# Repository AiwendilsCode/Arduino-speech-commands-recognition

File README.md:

# Arduino speech commands recognition
Arduino speech commands recognition is project in which I tried teach Arduino Nano recognizing words or commands using neural network. This project is inspirated by another [speech commands recognition project by Peter Balch](https://www.instructables.com/Speech-Recognition-With-an-Arduino-Nano/).
Difference between mine and Balch's project is that I used different algorithm for recognizing words.

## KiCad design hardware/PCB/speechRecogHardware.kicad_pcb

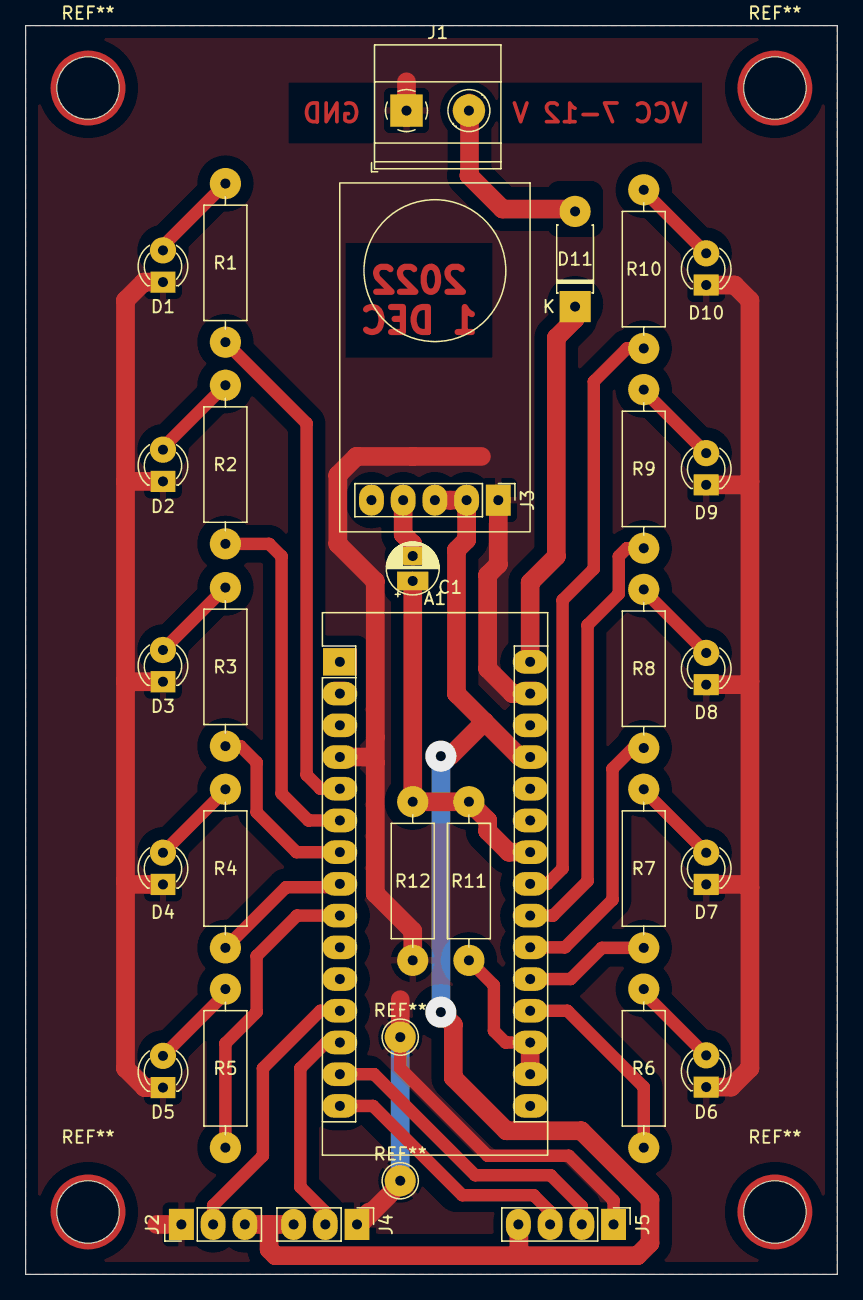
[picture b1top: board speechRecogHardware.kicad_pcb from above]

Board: 2 copper layers, 65.0 x 100.0 mm, 30 parts (0 on the bottom side), 31 nets.

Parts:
A1: Arduino_Nano
C1: 1u; CP_Radial_D4.0mm_P2.00mm
D1, D2, D3, D4, D5, D6, D7, D8, D9, D10: LED; LED_D3.0mm
D11: DIODE; D_DO-41_SOD81_P7.62mm_Horizontal
J1: PWR 6-12V; TerminalBlock_Phoenix_MKDS-1,5-2_1x02_P5.00mm_Horizontal
J2: servo1; PinHeader_1x03_P2.54mm_Vertical
J3: MAX9814_Mic; PinHeader_1x05_P2.54mm_Vertical
J4: servo2; PinHeader_1x03_P2.54mm_Vertical
J5: HC04; PinHeader_1x04_P2.54mm_Vertical
R1, R2, R3, R4, R5, R6, R7, R8, R9, R10: 300R; R_Axial_DIN0309_L9.0mm_D3.2mm_P12.70mm_Horizontal
R11, R12: 47k; R_Axial_DIN0309_L9.0mm_D3.2mm_P12.70mm_Horizontal

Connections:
+3V3: A1.17 (3V3), A1.18 (AREF), R11.2
+5V: A1.27 (+5V), J2.3, J3.2, J3.3, J4.3, J5.4
/OUT: C1.2, J3.4
GND: A1.4 (GND), A1.29 (GND), D1.1 (K), D2.1 (K), D3.1 (K), D4.1 (K), D5.1 (K), D6.1 (K), D7.1 (K), D8.1 (K), D9.1 (K), D10.1 (K), J1.1, J2.1, J3.1, J4.1, J5.1, R12.2
MIC_IN: A1.24 (A5), C1.1, R11.1, R12.1
unnamed: A1.5 (D2), R1.2
unnamed: A1.6 (D3), R2.2
unnamed: A1.7 (D4), R3.2
unnamed: A1.8 (D5), R4.2
unnamed: A1.9 (D6), R5.2
unnamed: A1.19 (A0), R6.2
unnamed: A1.20 (A1), R7.2
unnamed: A1.21 (A2), R8.2
unnamed: A1.22 (A3), R9.2
unnamed: A1.23 (A4), R10.2
unnamed: D1.2 (A), R1.1
unnamed: D2.2 (A), R2.1
unnamed: D3.2 (A), R3.1
unnamed: D4.2 (A), R4.1
unnamed: D5.2 (A), R5.1
unnamed: D6.2 (A), R6.1
unnamed: D7.2 (A), R7.1
unnamed: D8.2 (A), R8.1
unnamed: D9.2 (A), R9.1
unnamed: D10.2 (A), R10.1
unnamed: D11.1 (A), J1.2
VIN: A1.30 (VIN), D11.2 (K)
echo: A1.15 (D12), J5.3
servo1: A1.12 (D9(PWM)), J2.2
servo2: A1.13 (D10(PWM)), J4.2
trigger: A1.14 (D11), J5.2

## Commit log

2023-06-22 add hardware
2023-06-22 add arduino neural net
2023-06-22 add program for record dataset on arduino
2024-02-26 Add more project files.
2025-01-22 Add images and videos of final device.
